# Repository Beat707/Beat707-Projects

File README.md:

# Beat707 Projects
Created by William Kalfelz
www.Wusik.com
www.Kalfelz.com
www.Beat707.com

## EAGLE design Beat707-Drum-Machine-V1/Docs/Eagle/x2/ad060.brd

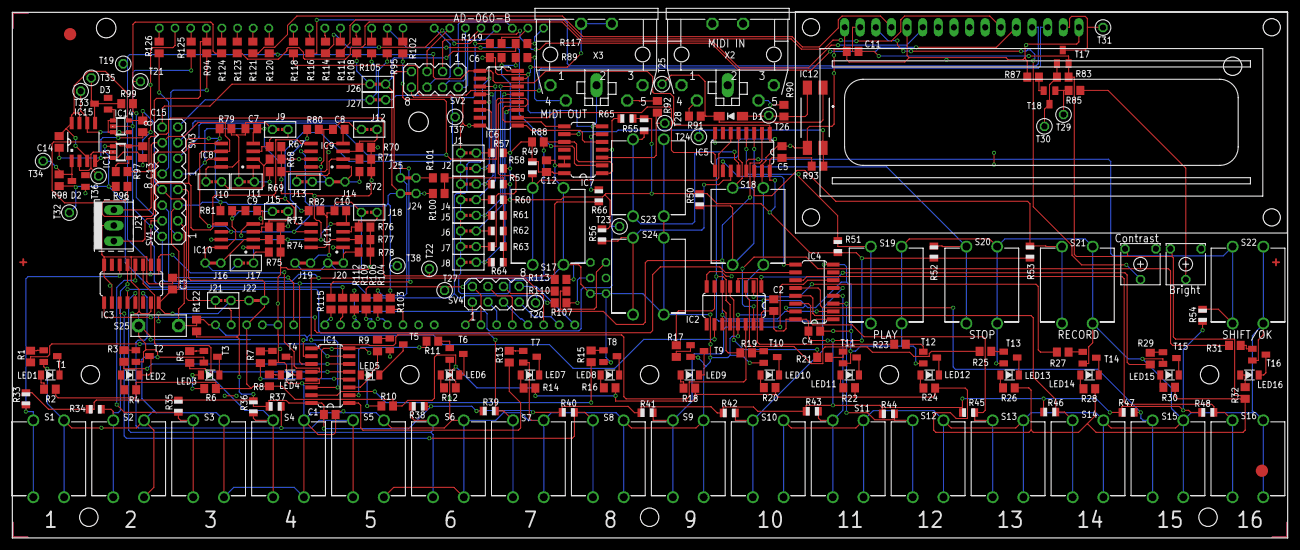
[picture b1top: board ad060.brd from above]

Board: 2 copper layers, 207.4 x 85.5 mm, 298 parts (0 on the bottom side), 206 nets.

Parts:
C1, C2, C3, C4, C5, C6, C7, C8, C9, C10, C11, C12, C13, C14, C15: 0.1uF; C0805
D1: SOD-123
D2, D3: 3.3V; SOT-23
FM1, FM2: FIDUCIAL2MMCIRCLE; FIDUCIAL_2MMCIRCLE
FM3, FM4: CROSSHAIR_12MIL
IC1, IC2: 74HC595D; SO16
IC3, IC4, IC5, IC6: 74HC165D; SO16
IC7: 74HC125D; SO14
IC8, IC9, IC10, IC11: M24256-BWMN6P; SO-08
IC12: LTV-817S; LITEON.SMD4
IC13, IC14: 74VHC1GT125D; SOT23-5
IC15: SST25VF040B; SO08
J1, J2, J3, J4, J5, J6, J7, J8, J9, J10, J11, J12, J13, J15, J17, J18, J21, J26, J27: JP2NO
J14, J16, J19, J20, J22, J24, J25: JP2NC
J23: CON3P1R.GC22232031; GC22232031
LED1, LED2, LED3, LED4, LED5, LED6, LED7, LED8, LED9, LED10, LED11, LED12, LED13, LED14, LED15, LED16: Red; LED1206
M1: Arduino UNO; SHIELD-NOTEXT-OCTAGONALPAD
M2: MEGA-EXTRAPINS-SPIONLY
R1, R3, R5, R7, R9, R11, R13, R15, R17, R19, R21, R23, R25, R27, R29, R31, R33, R34, R35, R36, R37, R38, R39, R40, R41, R42, R43, R44, R45, R46, R47, R48, R49, R50, R51, R52, R53, R54, R55, R56, R57, R58, R59, R60, R61, R62, R63, R64, R65, R67, R68, R69, R70, R71, R72, R73, R74, R75, R76, R77, R78, R83, R85, R88, R96, R122: 10k; R0805
R2, R4, R6, R8, R10, R12, R14, R16, R18, R20, R22, R24, R26, R28, R30, R32, R93: 300; R0805
R66, R94, R95, R97, R98, R99: 1k; R0805
R79, R80, R81, R82: 10; R0805
R84, R86: 10k; EVND8A
R87: 4.7k; R0805
R89, R90, R91, R92: 120; R0805
R100, R101: 1.5k; R0805
R102, R103, R104, R105, R106, R107, R108, R109, R110, R111, R112, R113, R114, R115, R116, R117, R118, R119, R120, R121, R123, R124, R125, R126: 100; R0805
S1, S2, S3, S4, S5, S6, S7, S8, S9, S10, S11, S12, S13, S14, S15, S16, S17, S18, S19, S20, S21, S22, S23, S24: TL1100F160Q
S25: EVQPJ
SV1, SV2, SV3, SV4: MA04-2
T1, T2, T3, T4, T5, T6, T7, T8, T9, T10, T11, T12, T13, T14, T15, T16, T18: NPN; SOT23-BEC
T17: PNP; SOT23-BEC
T19, T20, T21, T22, T23, T24, T25, T26, T27, T28, T29, T30, T31, T32, T33, T34, T35, T36, T37, T38: TP40MIL
U$1, U$3, U$4: CORNER-BL-NOARROW
U$2, U$6, U$7, U$8, U$10, U$11, U$12, U$13, U$14, U$15, U$16, U$17, U$18, U$19, U$20: 4-40SCREWHEXNUT
U$5: PB-MARK-0.2
U$9: ROHS-MARK-0.2
X1: 16x2; LCD1602
X2, X3: SDS-50J

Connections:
!RESET: IC1.10, IC2.10, M1.RESET, R122.1, S25.B, SV1.3
+3V3: C14.1, C15.1, IC14.5, IC15.3, IC15.7, IC15.8, J21.1, M1.3V3, SV1.8
+5V: C11.1, J22.2, M1.5V, R2.2, R4.2, R6.2, R8.2, R10.2, R12.2, R14.2, R16.2, R18.2, R20.2, R22.2, R24.2, R26.2, R28.2, R30.2, R32.2, R83.2, R84.3, R86.3, SV1.7, T17.E, X1.2
AREF: R126.1, SV3.2
D2: J27.1, R105.1, SV3.7
D3: J26.1, R108.1, SV3.8
D14: R115.2, SV2.7
FLASH_!SS: IC13.1, R96.1, R98.1, R112.2, T32.1
GND: C1.2, C2.2, C3.2, C4.2, C5.2, C6.2, C7.2, C8.2, C9.2, C10.2, C11.2, C12.2, C13.2, C14.2, C15.2, D2.1, D3.1, IC1.8, IC1.13, IC2.8, IC2.13, IC3.8, IC3.10, IC3.15, IC4.8, IC4.15, IC5.8, IC5.15, IC6.8, IC6.15, IC7.7, IC7.12, IC7.13, IC8.4, IC8.7, IC9.4, IC9.7, IC10.4, IC10.7, IC11.4, IC11.7, IC12.3, IC13.3, IC14.1, IC14.3, IC15.4, J1.1, J2.1, J3.1, J4.1, J5.1, J6.1, J7.1, J8.1, J23.2, M1.GND0, M1.GND1, M1.GND2, M2.GND@1, M2.GND@2, R67.1, R68.1, R69.1, R70.1, R71.1, R72.1, R73.1, R74.1, R75.1, R76.1, R77.1, R78.1, R84.1, R86.1, R87.1, S1.1, S1.2, S2.1, S2.2, S3.1, S3.2, S4.1, S4.2, S5.1, S5.2, S6.1, S6.2, S7.1, S7.2, S8.1, S8.2, S9.1, S9.2, S10.1, S10.2, S11.1, S11.2, S12.1, S12.2, S13.1, S13.2, S14.1, S14.2, S15.1, S15.2, S16.1, S16.2, S17.1, S17.2, S18.1, S18.2, S19.1, S19.2, S20.1, S20.2, S21.1, S21.2, S22.1, S22.2, S23.1, S23.2, S24.1, S24.2, S25.A, SV2.8, SV3.1, T1.E, T2.E, T3.E, T4.E, T5.E, T6.E, T7.E, T8.E, T9.E, T10.E, T11.E, T12.E, T13.E, T14.E, T15.E, T16.E, X1.1, X1.5, X1.16, X3.2, X3.PE, X3.PE@
LATCHOUT: IC1.12, IC2.12, IC3.1, IC4.1, IC5.1, IC6.1, R120.1, T19.1
LCD_D4: R111.1, X1.11
LCD_D5: R114.1, X1.12
LCD_D6: R116.1, X1.13
LCD_D7: R118.1, X1.14
LCD_E: R123.1, X1.6
LCD_RS: R121.1, X1.4
MIDI_EN: IC7.1, IC7.10, R88.1, R106.2, T27.1
unnamed: IC1.9, IC2.14
unnamed: M2.50, R113.2
unnamed: LED1.A, R2.1
unnamed: LED1.K, T1.C
unnamed: LED2.A, R4.1
unnamed: LED2.K, T2.C
unnamed: IC1.7, R1.2
unnamed: IC1.6, R3.2
unnamed: R3.1, T2.B
unnamed: IC13.4, R97.2
unnamed: M1.11, R124.2
unnamed: R1.1, T1.B
unnamed: M1.13, R125.2
unnamed: LED3.A, R6.1
unnamed: M2.51, R110.2
unnamed: IC3.9, IC4.10
unnamed: IC5.9, IC6.10
unnamed: M1.4, R111.2
unnamed: M1.6, R116.2
unnamed: IC5.6, R49.1, S17.3, S17.4
unnamed: M1.5, R114.2
unnamed: IC3.6, R33.1, S1.3, S1.4
unnamed: M1.7, R118.2
unnamed: IC3.5, R34.1, S2.3, S2.4
unnamed: M1.8, R120.2
unnamed: IC3.4, R35.1, S3.3, S3.4
unnamed: M1.A_1, R112.1
unnamed: IC3.3, R36.1, S4.3, S4.4
unnamed: M1.A_0, R115.1
unnamed: IC3.14, R37.1, S5.3, S5.4
unnamed: LED3.K, T3.C
unnamed: R5.1, T3.B
unnamed: IC3.13, R38.1, S6.3, S6.4
unnamed: IC3.12, R39.1, S7.3, S7.4
unnamed: IC4.6, R41.1, S9.3, S9.4
unnamed: IC4.5, R42.1, S10.3, S10.4
unnamed: IC8.1, J11.1, R69.2
unnamed: LED4.A, R8.1
unnamed: LED4.K, T4.C
unnamed: R7.1, T4.B
unnamed: IC8.2, J10.1, R68.2
unnamed: IC8.3, J9.1, R67.2
unnamed: IC4.4, R43.1, S11.3, S11.4
unnamed: IC3.11, R40.1, S8.3, S8.4
unnamed: IC4.3, R44.1, S12.3, S12.4
unnamed: IC4.14, R45.1, S13.3, S13.4
unnamed: IC4.13, R46.1, S14.3, S14.4
unnamed: IC4.12, R47.1, S15.3, S15.4
unnamed: IC4.11, R48.1, S16.3, S16.4
unnamed: IC5.5, R50.1, S18.3, S18.4
unnamed: IC5.4, R51.1, S19.3, S19.4
unnamed: IC5.3, R52.1, S20.3, S20.4
unnamed: IC5.14, R53.1, S21.3, S21.4
unnamed: IC5.13, R54.1, S22.3, S22.4
unnamed: LED5.A, R10.1
unnamed: LED5.K, T5.C
unnamed: R9.1, T5.B
unnamed: LED6.A, R12.1
unnamed: LED6.K, T6.C
unnamed: R11.1, T6.B
unnamed: LED7.A, R14.1
unnamed: LED7.K, T7.C
unnamed: R13.1, T7.B
unnamed: LED8.A, R16.1
unnamed: LED8.K, T8.C
unnamed: R15.1, T8.B
unnamed: LED9.A, R18.1
unnamed: LED9.K, T9.C
unnamed: LED10.A, R20.1
unnamed: LED10.K, T10.C
unnamed: R17.1, T9.B
unnamed: R19.1, T10.B
unnamed: LED11.A, R22.1
unnamed: LED11.K, T11.C
unnamed: R21.1, T11.B
unnamed: LED12.A, R24.1
unnamed: LED12.K, T12.C
unnamed: R23.1, T12.B
unnamed: LED13.A, R26.1
unnamed: LED13.K, T13.C
unnamed: R25.1, T13.B
unnamed: LED14.A, R28.1
unnamed: LED14.K, T14.C
unnamed: R27.1, T14.B
unnamed: LED15.A, R30.1
unnamed: LED15.K, T15.C
unnamed: R29.1, T15.B
unnamed: LED16.A, R32.1
unnamed: LED16.K, T16.C
unnamed: R31.1, T16.B
unnamed: IC1.5, R5.2
unnamed: IC1.4, R7.2
unnamed: IC1.3, R9.2
unnamed: IC1.2, R11.2
unnamed: IC1.1, R13.2
unnamed: IC1.15, R15.2
unnamed: IC2.7, R17.2
unnamed: IC2.6, R19.2
unnamed: IC2.5, R21.2
unnamed: IC2.4, R23.2
unnamed: IC2.3, R25.2
unnamed: IC2.2, R27.2
unnamed: IC2.1, R29.2
unnamed: IC2.15, R31.2
unnamed: IC5.12, R55.1, S23.3, S23.4
unnamed: IC5.11, R56.1, S24.3, S24.4
unnamed: IC6.6, J1.2, R57.1
unnamed: IC6.5, J2.2, R58.1
unnamed: IC6.4, J3.2, R59.1
unnamed: IC6.3, J4.2, R60.1
unnamed: IC6.14, J5.2, R61.1
unnamed: IC6.13, J6.2, R62.1
unnamed: IC6.12, J7.2, R63.1
unnamed: IC6.11, J8.2, R64.1
unnamed: R84.2, X1.3
unnamed: R89.1, X3.4
unnamed: T17.C, T31.1, X1.15
unnamed: IC9.1, J14.1, R72.2
unnamed: IC9.2, J13.1, R71.2
unnamed: IC9.3, J12.1, R70.2
unnamed: IC10.1, J17.1, R75.2
unnamed: IC10.2, J16.1, R74.2
unnamed: IC10.3, J15.1, R73.2
unnamed: IC11.1, J20.1, R78.2
unnamed: IC11.2, J19.1, R77.2
unnamed: IC11.3, J18.1, R76.2
unnamed: R83.1, T17.B, T18.C, T30.1
unnamed: R92.2, X3.5
unnamed: R87.2, T18.E
unnamed: R85.1, R86.2
unnamed: R85.2, T18.B, T29.1
unnamed: M1.0_RX, R102.2
unnamed: M1.A_3, R106.1
unnamed: M1.A_2, R109.1
unnamed: R91.1, X2.4
unnamed: R90.2, X2.5
unnamed: D1.K, IC12.1, R91.2, T25.1
unnamed: D1.A, IC12.2, R90.1, T26.1
unnamed: M1.9, R121.2
unnamed: M1.10, R123.2
unnamed: J24.2, R100.1
unnamed: J25.2, R101.1
unnamed: M2.21, R117.2
unnamed: M1.AREF, R126.2
unnamed: M2.20, R119.2
unnamed: M1.A_4, R104.1
unnamed: M1.A_5, R103.1
unnamed: M1.2, R105.2
unnamed: M1.3, R108.2
unnamed: M2.52, R107.2
unnamed: R95.1, SV3.5
unnamed: IC14.4, IC15.6, T33.1
unnamed: IC7.3, R92.1, T28.1
unnamed: IC13.2, IC15.2, T36.1
unnamed: IC7.9, IC12.4, R93.1, T24.1
unnamed: R94.1, SV1.1
unnamed: IC7.6, R66.2
unnamed: IC6.9, IC7.5
unnamed: D3.3, IC15.5, R99.2, T35.1
unnamed: D2.3, IC15.1, R98.2, T34.1
PD2: M2.19, SV2.1
PD3: M2.18, SV2.2
PH0: M2.17, SV2.3
PH1: M2.16, SV2.4
PJ0: M2.15, SV2.5
PJ1: M2.14, SV2.6
PK0: M2.A8, SV4.1
PK1: M2.A9, SV4.2
PK2: M2.A10, SV4.3
PK3: M2.A11, SV4.4
PK4: M2.A12, SV4.5
PK5: M2.A13, SV4.6
PK6: M2.A14, SV4.7
PK7: M2.A15, SV4.8
SCL: IC8.6, IC9.6, IC10.6, IC11.6, J23.3, J24.1, J26.2, R103.2, R117.1, SV3.6, T38.1
SDA: IC8.5, IC9.5, IC10.5, IC11.5, J23.1, J25.1, J27.2, R104.2, R119.1, SV3.4, T37.1
SHIFTMIDDLE: IC4.9, IC5.10
SPI_CLK: IC1.11, IC2.11, IC3.2, IC4.2, IC5.2, IC6.2, IC14.2, R107.1, R125.1, SV1.4, T20.1
SPI_MISO: M1.12, R66.1, R94.2, R97.1, R113.1, T22.1
SPI_MOSI: IC1.14, R99.1, R110.1, R124.1, SV1.2, T21.1
SWITCH_!SS: IC7.4, R65.1, R109.2, T23.1
UART_RX: IC7.8, R102.1, SV3.3
UART_TX: IC7.2, M1.1_TX, R95.2
V+: C1.1, C2.1, C3.1, C4.1, C5.1, C6.1, C12.1, C13.1, IC1.16, IC2.16, IC3.16, IC4.16, IC5.16, IC6.16, IC7.14, IC13.5, J21.2, J22.1, R33.2, R34.2, R35.2, R36.2, R37.2, R38.2, R39.2, R40.2, R41.2, R42.2, R43.2, R44.2, R45.2, R46.2, R47.2, R48.2, R49.2, R50.2, R51.2, R52.2, R53.2, R54.2, R55.2, R56.2, R57.2, R58.2, R59.2, R60.2, R61.2, R62.2, R63.2, R64.2, R65.2, R79.1, R80.1, R81.1, R82.1, R88.2, R89.2, R93.2, R96.2, R100.2, R101.2, R122.2, SV1.5
V+_E1: C7.1, IC8.8, J9.2, J10.2, J11.2, R79.2
V+_E2: C8.1, IC9.8, J12.2, J13.2, J14.2, R80.2
V+_E3: C9.1, IC10.8, J15.2, J16.2, J17.2, R81.2
V+_E4: C10.1, IC11.8, J18.2, J19.2, J20.2, R82.2
VIN: M1.VIN, SV1.6

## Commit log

2019-04-22 Initial
2019-04-22 Updated Folder Names
